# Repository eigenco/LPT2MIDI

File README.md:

# LPT2MIDI
- LPT2MIDI is a parallel printer port (LPT) to MIDI adapter.
- Autodesk Eagle PCB files are included.
- Uses Arduino IRQ to trigger pin reads and forwards the data to MIDI serial buffer (MIDI uses 31250 bps).
- A simple port trapping code for MS-DOS is included. This for the time being works for direct midi commands to port 330h only.
- Quickly modified version of SOFTMPU for MPU-401 compatibility.
- Tested with Roland MT-32 and Supaplex (an old MS-DOS game, requires minor modification to the code).
- Requires power through USB while operating.

Youtube link of the device in action: https://www.youtube.com/watch?v=MyJpt-w3Oao

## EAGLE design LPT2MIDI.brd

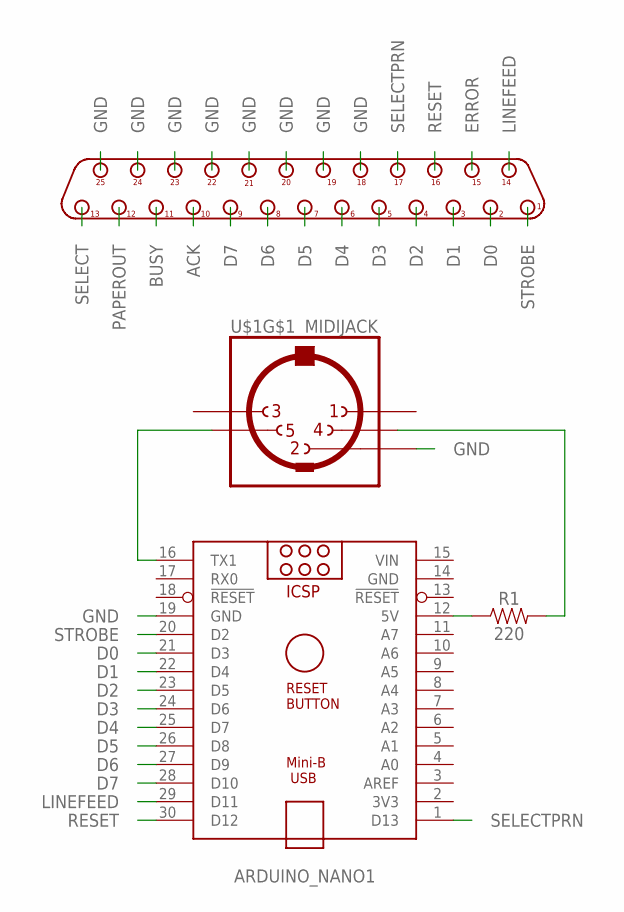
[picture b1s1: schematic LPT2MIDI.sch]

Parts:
ARDUINO_NANO1: ARDUINO_NANO
CON1: DB25M/90; D-25M/90
R1: 220; AXIAL-0.3
U$1: MIDIJACK; CP-2350

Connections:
ACK: CON1.10
BUSY: CON1.11
D0: ARDUINO_NANO1.21 (D3), CON1.2
D1: ARDUINO_NANO1.22 (D4), CON1.3
D2: ARDUINO_NANO1.23 (D5), CON1.4
D3: ARDUINO_NANO1.24 (D6), CON1.5
D4: ARDUINO_NANO1.25 (D7), CON1.6
D5: ARDUINO_NANO1.26 (D8), CON1.7
D6: ARDUINO_NANO1.27 (D9), CON1.8
D7: ARDUINO_NANO1.28 (D10), CON1.9
ERROR: CON1.15
GND: ARDUINO_NANO1.14 (GND), ARDUINO_NANO1.19 (GND), CON1.18, CON1.19, CON1.20, CON1.21, CON1.22, CON1.23, CON1.24, CON1.25, U$1.2
LINEFEED: ARDUINO_NANO1.29 (D11), CON1.14
unnamed: ARDUINO_NANO1.12 (5V), R1.P$1 (1)
unnamed: R1.P$2 (2), U$1.4
unnamed: ARDUINO_NANO1.16 (TX1), U$1.5
PAPEROUT: CON1.12
RESET: ARDUINO_NANO1.30 (D12), CON1.16
SELECT: CON1.13
SELECTPRN: ARDUINO_NANO1.1 (D13), CON1.17
STROBE: ARDUINO_NANO1.20 (D2), CON1.1
VIN: ARDUINO_NANO1.15 (VIN)

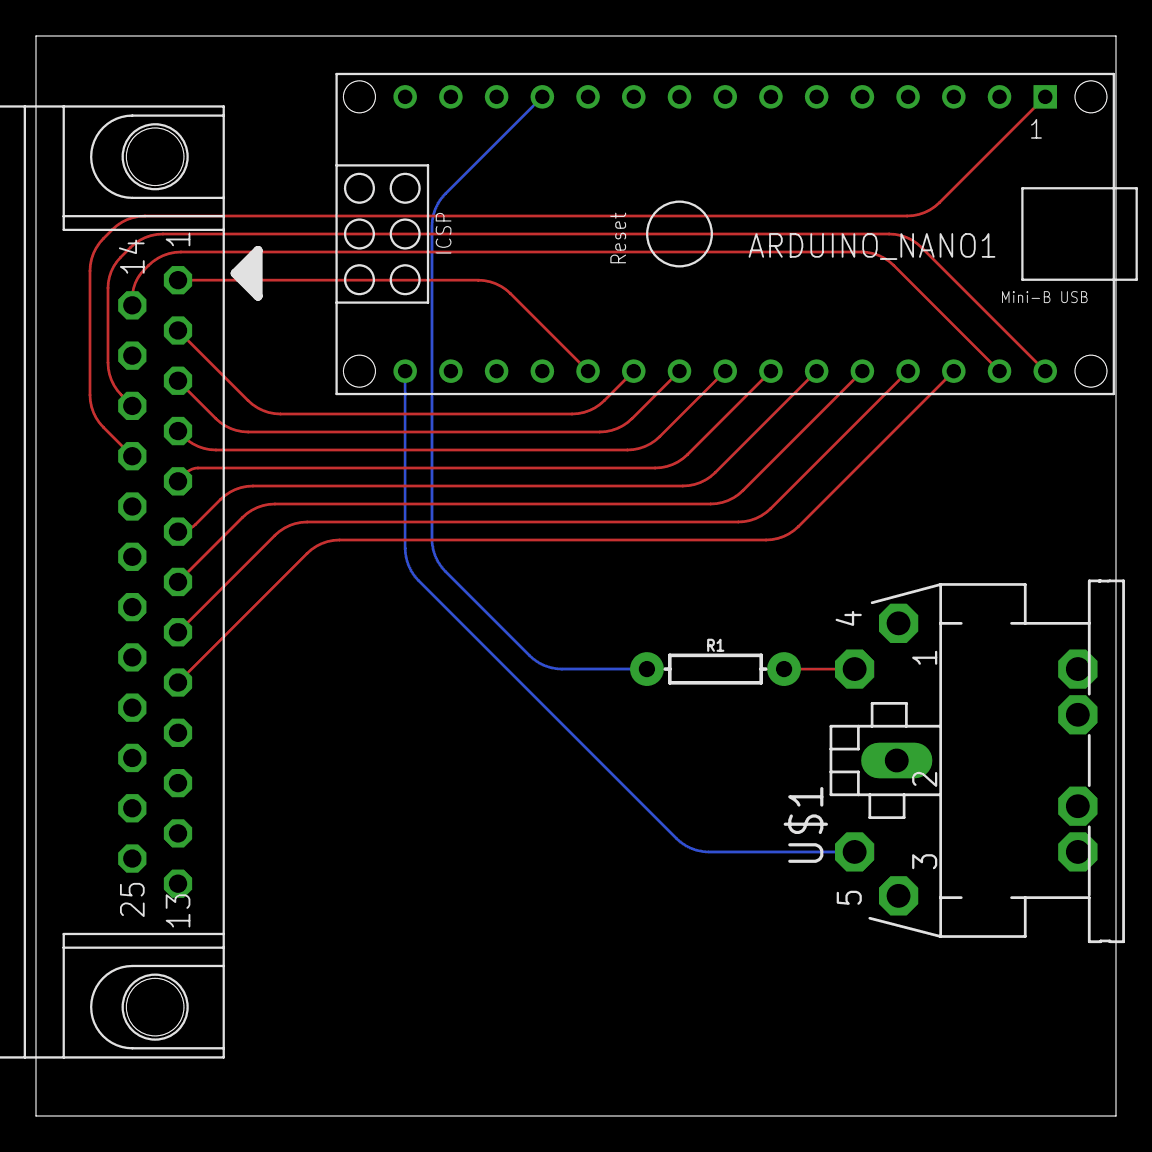
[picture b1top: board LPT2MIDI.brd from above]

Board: 2 copper layers, 60.0 x 60.0 mm, 4 parts (0 on the bottom side), 16 nets.

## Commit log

2021-12-21 Improved interrupt timing behaviour.
    Removed the Serial.write() call from the interrupt routine. Added a
    FIFO buffer to accumulate the data and moved the Serial.write() into
    the main loop. Now the interrupt should come back almost instantly.
2021-12-29 Fix timing issues and an fifo wrap bug
2021-12-30 Fix some typos

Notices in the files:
parts and their libraries:
SparkFun-Resistors: Licensing: Creative Commons ShareAlike 4.0 International - https://creativecommons.org/licenses/by-sa/4.0
